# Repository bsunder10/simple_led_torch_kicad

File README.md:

# simple_led_torch_kicad

New Project

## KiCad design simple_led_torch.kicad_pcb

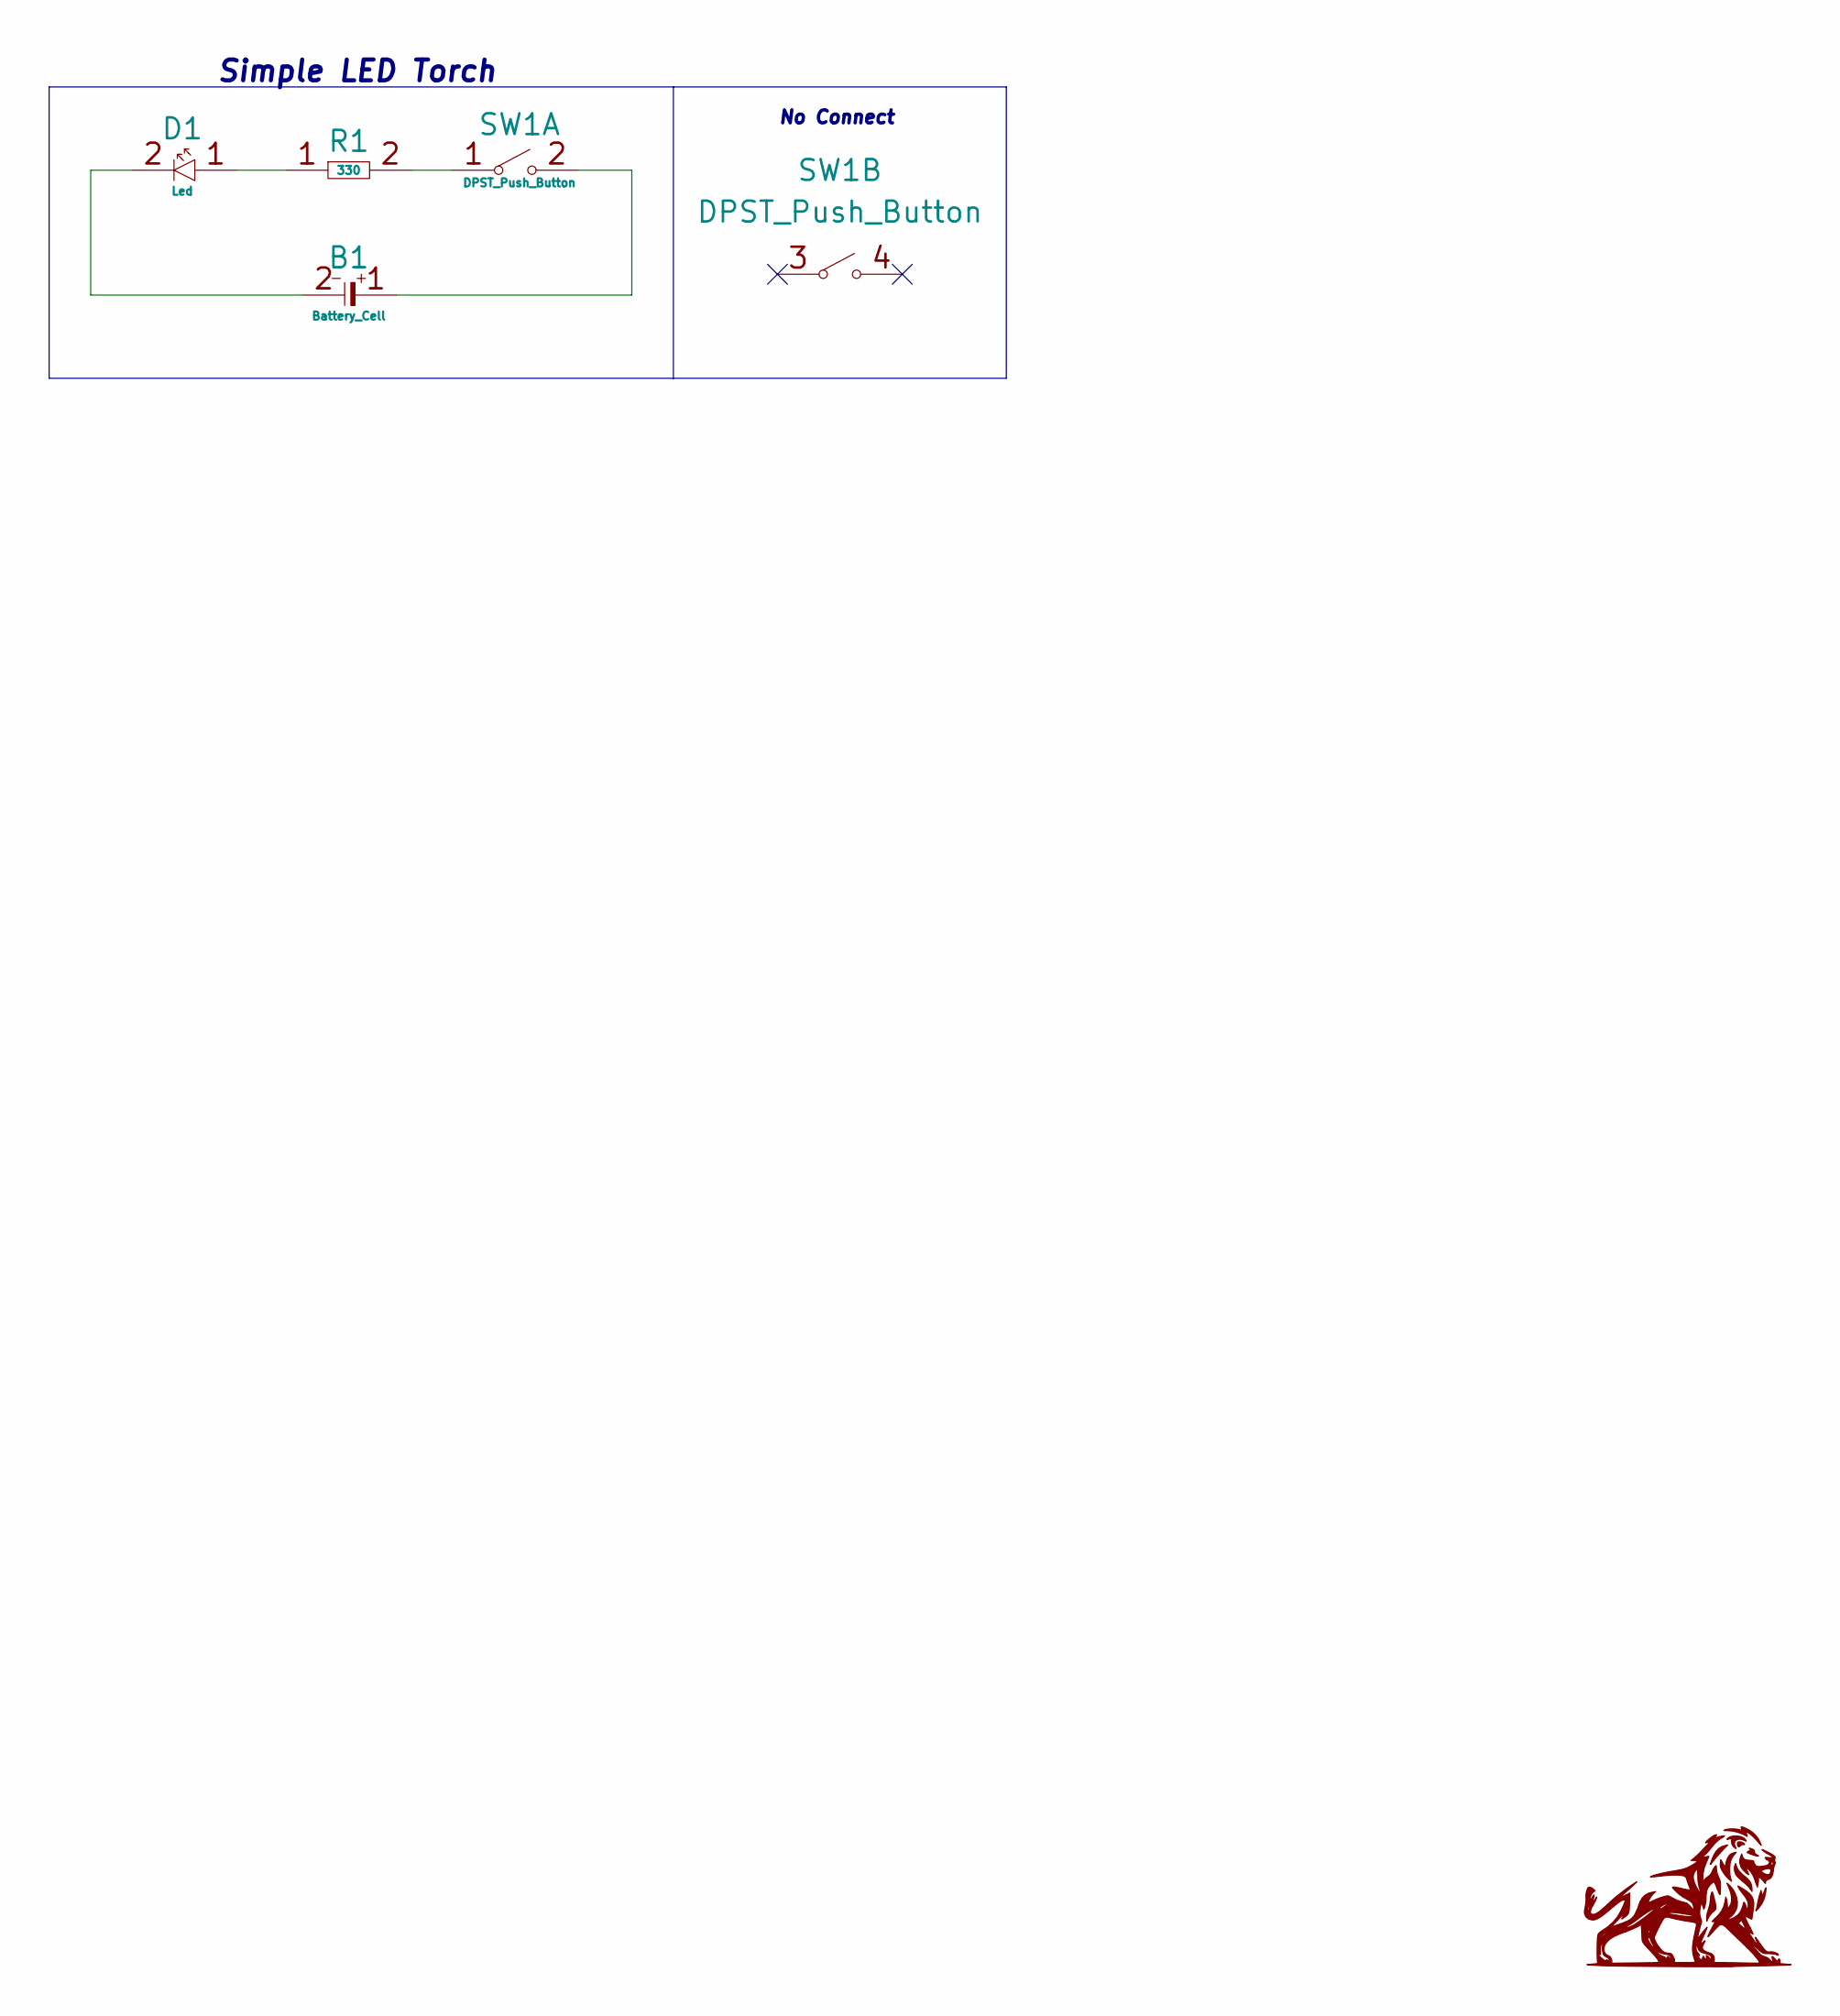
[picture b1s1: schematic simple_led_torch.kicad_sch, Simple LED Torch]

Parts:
B1: Battery_Cell; 2032_Battery_Holder; Part Number 534-1058
D1: Led; LED_L10mm_D2.54mm; Part Number 593-VAOL-10GWY4
R1: 330; R_Axial_L8mm_D2.5mm_Horizontal; Part Number 66-SPP2UL3300JLF
SW1: DPST_Push_Button; DPST_L6.5mm_D4.5mm; Part Number 179-TS0266110BK160SC

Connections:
unnamed: B1.1, SW1.2
unnamed: B1.2, D1.2
unnamed: D1.1, R1.1
unnamed: R1.2, SW1.1

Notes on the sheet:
No Connect
Simple LED Torch

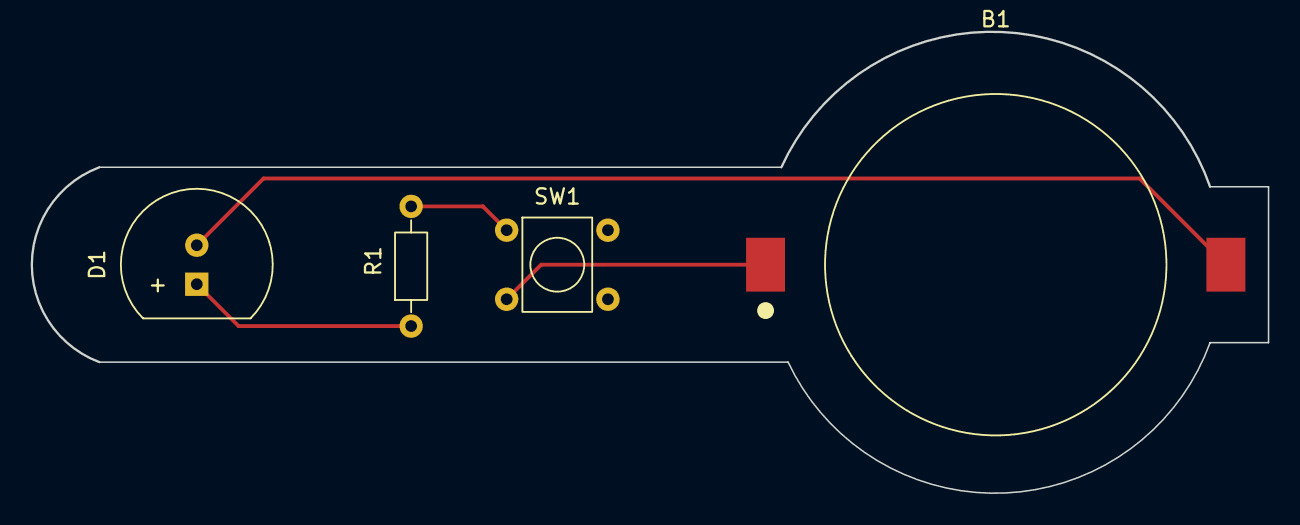
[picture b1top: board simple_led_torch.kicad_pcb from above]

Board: 2 copper layers, 80.6 x 30.0 mm, 4 parts (0 on the bottom side), 4 nets.

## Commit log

2022-01-26 project
2022-01-26 Schematic
2022-01-26 Start of Footprints
2022-01-27 few footprints
2022-01-27 confirm previous commit
2022-01-28 update footprints
2022-01-29 PCB Layout
2022-01-30 done
2022-02-06 Added 3d models
